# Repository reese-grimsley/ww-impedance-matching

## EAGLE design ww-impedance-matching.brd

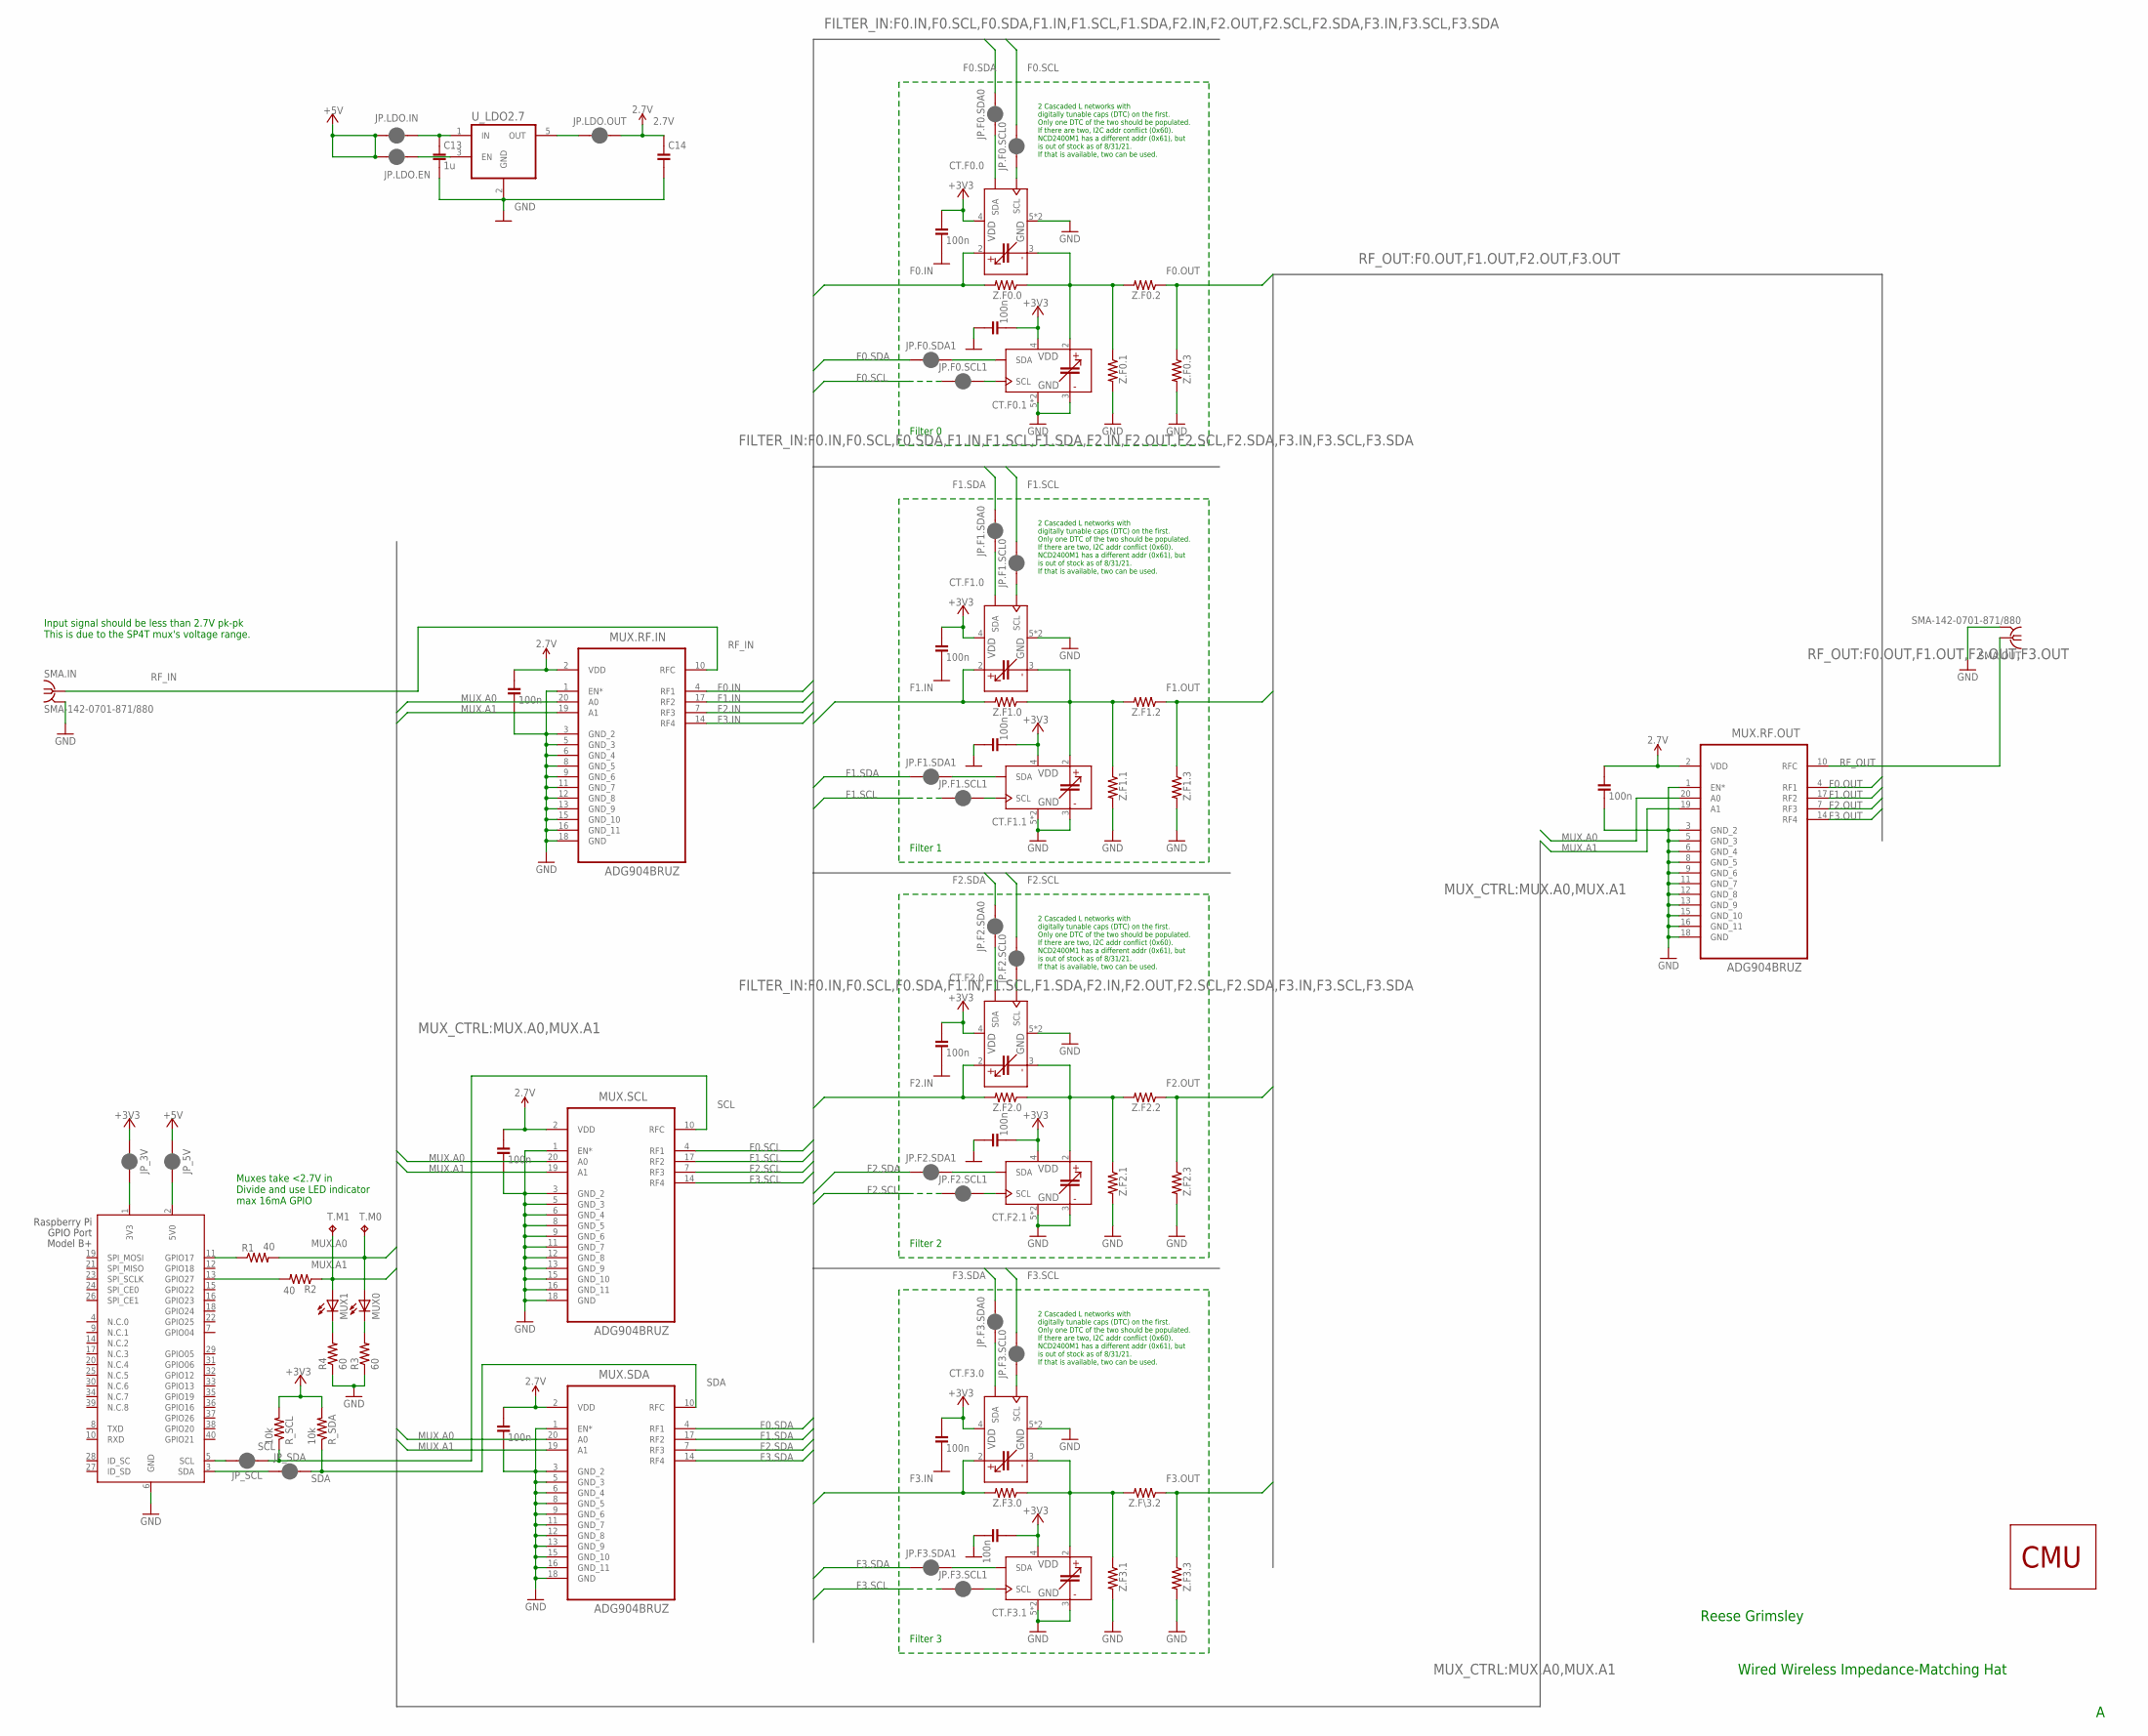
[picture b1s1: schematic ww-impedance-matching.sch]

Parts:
C1, C2, C3, C4, C5, C6, C7, C8, C9, C10, C11, C12: 100n; C0603; MPN CC0603MRX7R7BB104
C13: 1u; C0603; MPN CC0603MRX5R8BB105
C14: C-0805; C0805; MPN CC0805KPX5R6BB106
CT.F0.0, CT.F0.1, CT.F1.0, CT.F1.1, CT.F2.0, CT.F2.1, CT.F3.0, CT.F3.1: TUNABLE_CAP_NCD2400MTR; DFN-6_NCD2400M
JP.F0.SCL0, JP.F0.SCL1, JP.F0.SDA0, JP.F0.SDA1, JP.F1.SCL0, JP.F1.SCL1, JP.F1.SDA0, JP.F1.SDA1, JP.F2.SCL0, JP.F2.SCL1, JP.F2.SDA0, JP.F2.SDA1, JP.F3.SCL0, JP.F3.SCL1, JP.F3.SDA0, JP.F3.SDA1, JP.LDO.EN, JP.LDO.IN, JP.LDO.OUT: JUMPER-SMT_2_NC_PASTE_NO-SILK; SMT-JUMPER_2_NC_PASTE_NO-SILK
JP_3V, JP_5V: JUMPER-SMT_2_NC_PASTE_NO-SILK; SMT-JUMPER_2_NC_PASTE_NO-SILK
JP_SCL: JUMPER-SMT_2_NC_PASTE_NO-SILK; SMT-JUMPER_2_NC_PASTE_NO-SILK
JP_SDA: JUMPER-SMT_2_NC_PASTE_NO-SILK; SMT-JUMPER_2_NC_PASTE_NO-SILK
LOGO1: LOGO-CMU; CMU_LOGO
MUX0, MUX1: LEDCHIPLED_0603; CHIPLED_0603; MPN LSM0603412V
MUX.RF.IN, MUX.RF.OUT, MUX.SCL, MUX.SDA: ADG904BRUZ; SOP65P640X120-20N
R1, R2: 40; R0603; MPN ERJ-3EKF40R2V
R3, R4: 60; R0603; MPN ERJ-3EKF60R4V
R_SCL: 10k; R0603; MPN ERJ-PA3F1002V
R_SDA: 10k; R0603; MPN ERJ-PA3F1002V
SMA.IN, SMA.OUT: SMA-142-0701-871/880; SMA-142-0701-871; PART_NO 142-0701-871
T.M0, T.M1: TPTP14R; TP14R
U_LDO2.7: TPS76327DBVT; SOT95P280X145-5N; MPN TPS76327DBVT
X1: RASPI_BOARD_B+_E4P; RASPI_BOARD_B+_EDGES_4DRILL_PAD; MPN TSM-110-02-S-DV
Z.F0.0, Z.F0.1, Z.F0.2, Z.F0.3, Z.F1.0, Z.F1.1, Z.F1.2, Z.F1.3, Z.F2.0, Z.F2.1, Z.F2.2, Z.F2.3, Z.F3.0, Z.F3.1, Z.F3.3, Z.F\3.2: R-0603; R0603

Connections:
2.7V: C7.1, C9.1, C11.1, C12.1, C14.1, JP.LDO.OUT.1, MUX.RF.IN.2 (VDD), MUX.RF.OUT.2 (VDD), MUX.SCL.2 (VDD), MUX.SDA.2 (VDD)
3V3.JMP: JP_3V.1, X1.1 (3V3)
5V.JMP: JP_5V.1, X1.2 (5V0)
+3V3: C1.1, C2.2, C3.1, C4.1, C5.1, C6.2, C8.1, C10.2, CT.F0.0.4 (VDD), CT.F0.1.4 (VDD), CT.F1.0.4 (VDD), CT.F1.1.4 (VDD), CT.F2.0.4 (VDD), CT.F2.1.4 (VDD), CT.F3.0.4 (VDD), CT.F3.1.4 (VDD), JP_3V.2, R_SCL.2, R_SDA.2
+5V: JP.LDO.EN.2, JP.LDO.IN.2, JP_5V.2
F0.IN: CT.F0.0.2 (C+), MUX.RF.IN.4 (RF1), Z.F0.0.2
F0.OUT: MUX.RF.OUT.4 (RF1), Z.F0.2.1, Z.F0.3.1
F0.SCL: JP.F0.SCL0.1, JP.F0.SCL1.2, MUX.SCL.4 (RF1)
F0.SDA: JP.F0.SDA0.1, JP.F0.SDA1.2, MUX.SDA.4 (RF1)
F0SCL0: CT.F0.0.6 (SCL), JP.F0.SCL0.2
F0SCL1: CT.F0.1.6 (SCL), JP.F0.SCL1.1
F0SDA0: CT.F0.0.1 (SDA), JP.F0.SDA0.2
F0SDA1: CT.F0.1.1 (SDA), JP.F0.SDA1.1
F1.IN: CT.F1.0.2 (C+), MUX.RF.IN.17 (RF2), Z.F1.0.2
F1.OUT: MUX.RF.OUT.17 (RF2), Z.F1.2.1, Z.F1.3.1
F1.SCL: JP.F1.SCL0.1, JP.F1.SCL1.2, MUX.SCL.17 (RF2)
F1.SDA: JP.F1.SDA0.1, JP.F1.SDA1.2, MUX.SDA.17 (RF2)
F1SCL0: CT.F1.0.6 (SCL), JP.F1.SCL0.2
F1SCL1: CT.F1.1.6 (SCL), JP.F1.SCL1.1
F1SDA0: CT.F1.0.1 (SDA), JP.F1.SDA0.2
F1SDA1: CT.F1.1.1 (SDA), JP.F1.SDA1.1
F2.IN: CT.F2.0.2 (C+), MUX.RF.IN.7 (RF3), Z.F2.0.2
F2.OUT: MUX.RF.OUT.7 (RF3), Z.F2.2.1, Z.F2.3.1
F2.SCL: JP.F2.SCL0.1, JP.F2.SCL1.2, MUX.SCL.7 (RF3)
F2.SDA: JP.F2.SDA0.1, JP.F2.SDA1.2, MUX.SDA.7 (RF3)
F2SCL0: CT.F2.0.6 (SCL), JP.F2.SCL0.2
F2SCL1: CT.F2.1.6 (SCL), JP.F2.SCL1.1
F2SDA0: CT.F2.0.1 (SDA), JP.F2.SDA0.2
F2SDA1: CT.F2.1.1 (SDA), JP.F2.SDA1.1
F3.IN: CT.F3.0.2 (C+), MUX.RF.IN.14 (RF4), Z.F3.0.2
F3.OUT: MUX.RF.OUT.14 (RF4), Z.F3.3.1, Z.F\3.2.1
F3.SCL: JP.F3.SCL0.1, JP.F3.SCL1.2, MUX.SCL.14 (RF4)
F3.SDA: JP.F3.SDA0.1, JP.F3.SDA1.2, MUX.SDA.14 (RF4)
F3SCL0: CT.F3.0.6 (SCL), JP.F3.SCL0.2
F3SCL1: CT.F3.1.6 (SCL), JP.F3.SCL1.1
F3SDA0: CT.F3.0.1 (SDA), JP.F3.SDA0.2
F3SDA1: CT.F3.1.1 (SDA), JP.F3.SDA1.1
GND: C1.2, C2.1, C3.2, C4.2, C5.2, C6.1, C7.2, C8.2, C9.2, C10.1, C11.2, C12.2, C13.2, C14.2, CT.F0.0.5 (GND), CT.F0.0.7 (GND), CT.F0.1.3 (C-), CT.F0.1.5 (GND), CT.F0.1.7 (GND), CT.F1.0.5 (GND), CT.F1.0.7 (GND), CT.F1.1.3 (C-), CT.F1.1.5 (GND), CT.F1.1.7 (GND), CT.F2.0.5 (GND), CT.F2.0.7 (GND), CT.F2.1.3 (C-), CT.F2.1.5 (GND), CT.F2.1.7 (GND), CT.F3.0.5 (GND), CT.F3.0.7 (GND), CT.F3.1.3 (C-), CT.F3.1.5 (GND), CT.F3.1.7 (GND), MUX.RF.IN.1 (EN*), MUX.RF.IN.3 (GND_2), MUX.RF.IN.5 (GND_3), MUX.RF.IN.6 (GND_4), MUX.RF.IN.8 (GND_5), MUX.RF.IN.9 (GND_6), MUX.RF.IN.11 (GND_7), MUX.RF.IN.12 (GND_8), MUX.RF.IN.13 (GND_9), MUX.RF.IN.15 (GND_10), MUX.RF.IN.16 (GND_11), MUX.RF.IN.18 (GND), MUX.RF.OUT.1 (EN*), MUX.RF.OUT.3 (GND_2), MUX.RF.OUT.5 (GND_3), MUX.RF.OUT.6 (GND_4), MUX.RF.OUT.8 (GND_5), MUX.RF.OUT.9 (GND_6), MUX.RF.OUT.11 (GND_7), MUX.RF.OUT.12 (GND_8), MUX.RF.OUT.13 (GND_9), MUX.RF.OUT.15 (GND_10), MUX.RF.OUT.16 (GND_11), MUX.RF.OUT.18 (GND), MUX.SCL.1 (EN*), MUX.SCL.3 (GND_2), MUX.SCL.5 (GND_3), MUX.SCL.6 (GND_4), MUX.SCL.8 (GND_5), MUX.SCL.9 (GND_6), MUX.SCL.11 (GND_7), MUX.SCL.12 (GND_8), MUX.SCL.13 (GND_9), MUX.SCL.15 (GND_10), MUX.SCL.16 (GND_11), MUX.SCL.18 (GND), MUX.SDA.1 (EN*), MUX.SDA.3 (GND_2), MUX.SDA.5 (GND_3), MUX.SDA.6 (GND_4), MUX.SDA.8 (GND_5), MUX.SDA.9 (GND_6), MUX.SDA.11 (GND_7), MUX.SDA.12 (GND_8), MUX.SDA.13 (GND_9), MUX.SDA.15 (GND_10), MUX.SDA.16 (GND_11), MUX.SDA.18 (GND), R3.1, R4.1, SMA.IN.2@1 (2), SMA.IN.2@2 (2), SMA.IN.2@3 (2), SMA.IN.2@4 (2), SMA.OUT.2@1 (2), SMA.OUT.2@2 (2), SMA.OUT.2@3 (2), SMA.OUT.2@4 (2), U_LDO2.7.2 (GND), X1.6 (GND), Z.F0.1.2, Z.F0.3.2, Z.F1.1.2, Z.F1.3.2, Z.F2.1.2, Z.F2.3.2, Z.F3.1.2, Z.F3.3.2
LDO.IN: C13.1, JP.LDO.IN.1, U_LDO2.7.1 (IN)
LDO.OUT: JP.LDO.OUT.2, U_LDO2.7.5 (OUT)
MUX.A0: MUX0.A, MUX.RF.IN.20 (A0), MUX.RF.OUT.20 (A0), MUX.SCL.20 (A0), MUX.SDA.20 (A0), R1.2, T.M0.TP
MUX.A1: MUX1.A, MUX.RF.IN.19 (A1), MUX.RF.OUT.19 (A1), MUX.SCL.19 (A1), MUX.SDA.19 (A1), R2.1, T.M1.TP
unnamed: MUX1.C, R4.2
unnamed: JP.LDO.EN.1, U_LDO2.7.3 (EN)
unnamed: MUX0.C, R3.2
unnamed: R2.2, X1.13 (GPIO27)
unnamed: R1.1, X1.11 (GPIO17)
RF.F0.0: CT.F0.0.3 (C-), CT.F0.1.2 (C+), Z.F0.0.1, Z.F0.1.1, Z.F0.2.2
RF.F1.0: CT.F1.0.3 (C-), CT.F1.1.2 (C+), Z.F1.0.1, Z.F1.1.1, Z.F1.2.2
RF.F2.0: CT.F2.0.3 (C-), CT.F2.1.2 (C+), Z.F2.0.1, Z.F2.1.1, Z.F2.2.2
RF.F3.0: CT.F3.0.3 (C-), CT.F3.1.2 (C+), Z.F3.0.1, Z.F3.1.1, Z.F\3.2.2
RF_IN: MUX.RF.IN.10 (RFC), SMA.IN.1
RF_OUT: MUX.RF.OUT.10 (RFC), SMA.OUT.1
SCL: JP_SCL.2, MUX.SCL.10 (RFC), R_SCL.1
SCL.IN: JP_SCL.1, X1.5 (SCL)
SDA: JP_SDA.1, MUX.SDA.10 (RFC), R_SDA.1
SDA.IN: JP_SDA.2, X1.3 (SDA)

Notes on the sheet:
Wired Wireless Impedance-Matching Hat
Filter 0
2 Cascaded L networks with digitally tunable caps (DTC) on the first. Only one DTC of the two should be populated. If there are two, I2C addr conflict (0x60). NCD2400M1 has a different addr (0x61), but is out of stock as of 8/31/21. If that is available, two can be used.
Filter 1
Filter 2
Reese Grimsley
Filter 3
Muxes take <2.7V in Divide and use LED indicator max 16mA GPIO
Input signal should be less than 2.7V pk-pk This is due to the SP4T mux's voltage range.

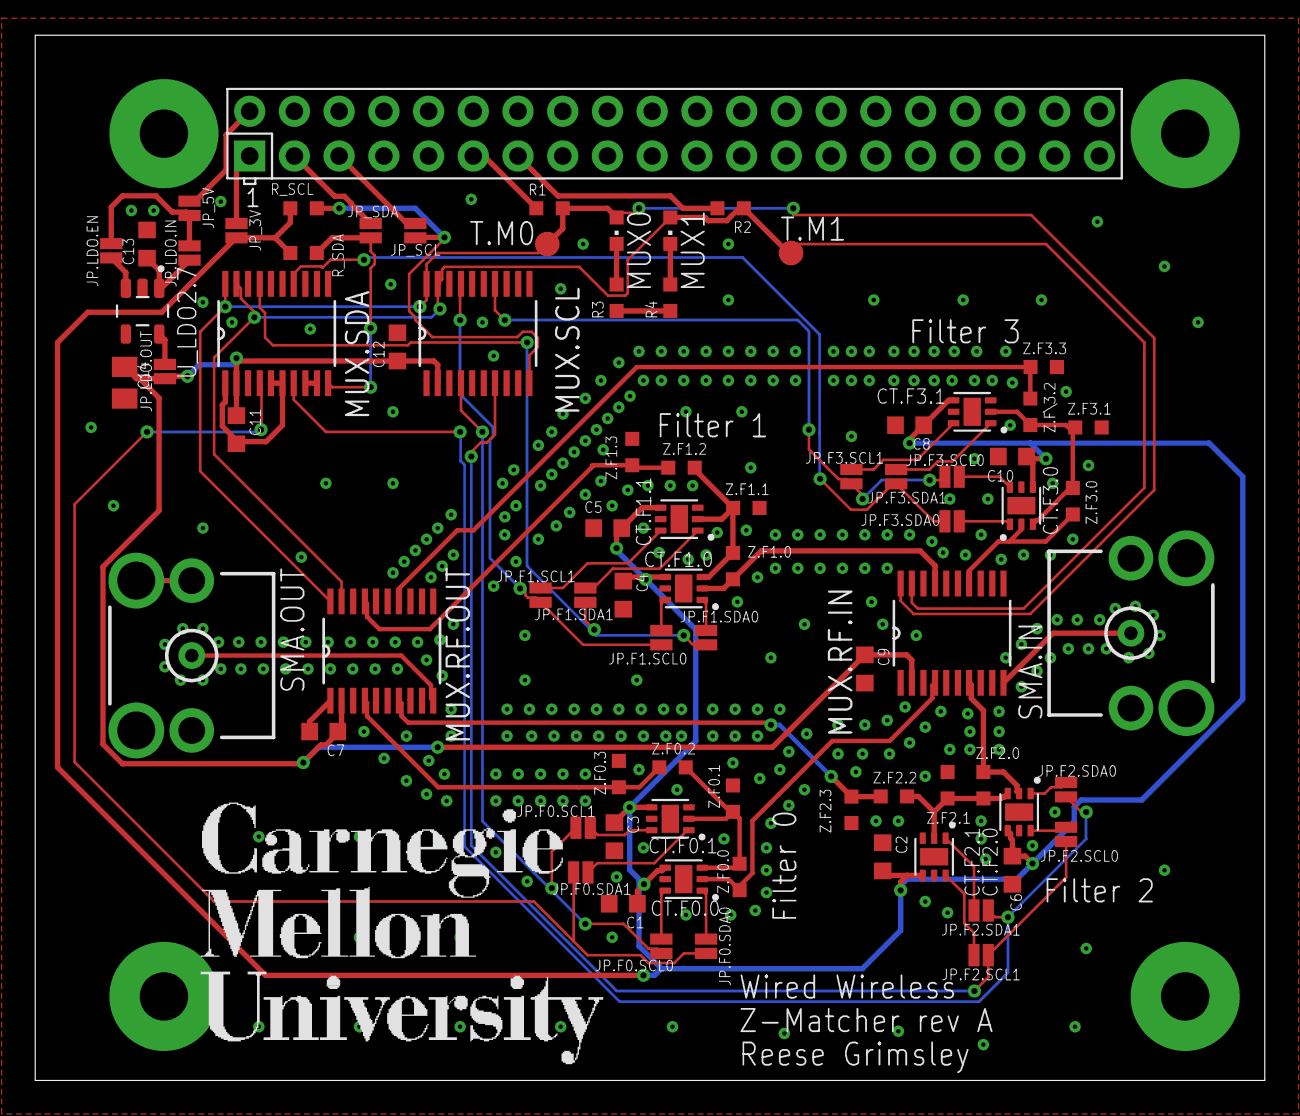
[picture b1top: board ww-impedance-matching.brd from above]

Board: 2 copper layers, 69.8 x 59.4 mm, 80 parts (0 on the bottom side), 57 nets.

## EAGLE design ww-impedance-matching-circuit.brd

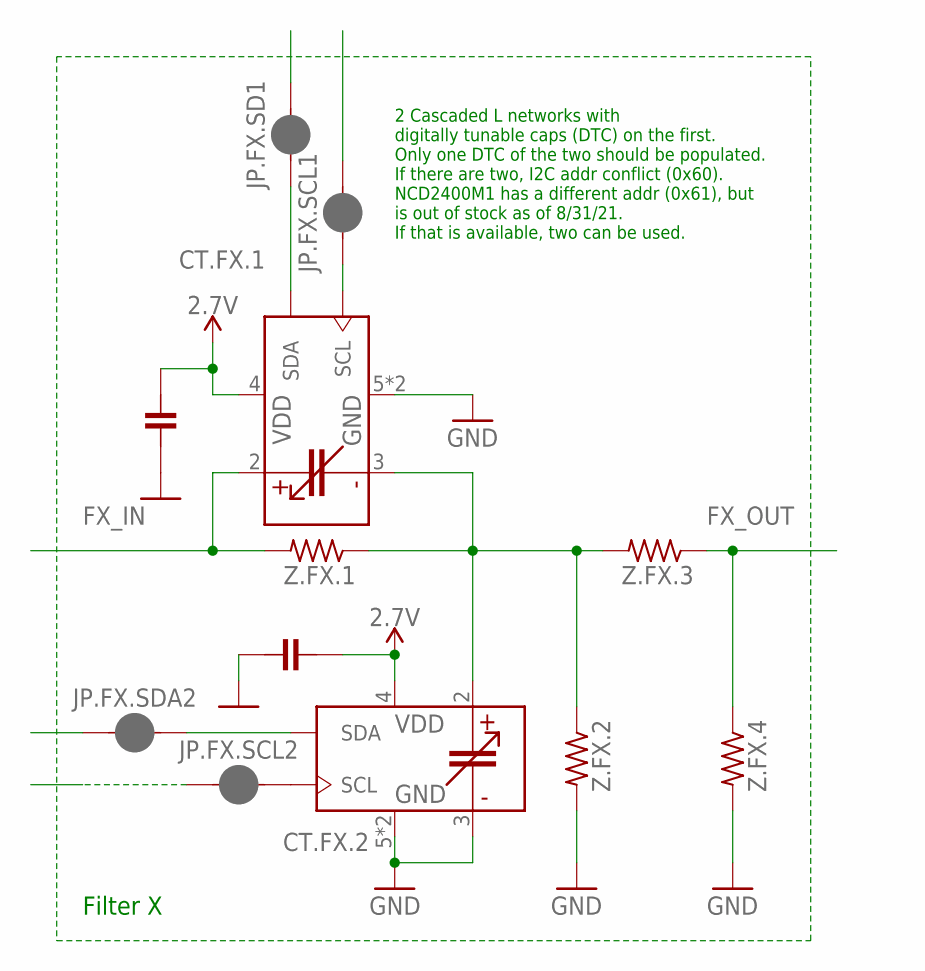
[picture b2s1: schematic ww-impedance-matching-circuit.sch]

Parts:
C1, C2: C-0603; C0603
CT.FX.1, CT.FX.2: TUNABLE_CAP_NCD2400MTR; DFN-6_NCD2400M
JP.FX.SCL1, JP.FX.SCL2, JP.FX.SD1, JP.FX.SDA2: JUMPER-SMT_2_NC_PASTE_NO-SILK; SMT-JUMPER_2_NC_PASTE_NO-SILK
Z.FX.1, Z.FX.2, Z.FX.3, Z.FX.4: R-0603; R0603

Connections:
2.7V: C1.1, C2.1, CT.FX.1.4 (VDD), CT.FX.2.4 (VDD)
FX_IN: CT.FX.1.2 (C+), Z.FX.1.2
FX_OUT: Z.FX.3.1, Z.FX.4.1
GND: C1.2, C2.2, CT.FX.1.5 (GND), CT.FX.1.7 (GND), CT.FX.2.3 (C-), CT.FX.2.5 (GND), CT.FX.2.7 (GND), Z.FX.2.2, Z.FX.4.2
unnamed: CT.FX.1.3 (C-), CT.FX.2.2 (C+), Z.FX.1.1, Z.FX.2.1, Z.FX.3.2
unnamed: CT.FX.1.1 (SDA), JP.FX.SD1.2
unnamed: CT.FX.2.1 (SDA), JP.FX.SDA2.1
unnamed: CT.FX.2.6 (SCL), JP.FX.SCL2.1
unnamed: CT.FX.1.6 (SCL), JP.FX.SCL1.2

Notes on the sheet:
Filter X
2 Cascaded L networks with digitally tunable caps (DTC) on the first. Only one DTC of the two should be populated. If there are two, I2C addr conflict (0x60). NCD2400M1 has a different addr (0x61), but is out of stock as of 8/31/21. If that is available, two can be used.

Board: 2 copper layers, 12 parts (0 on the bottom side), 9 nets, no tracks yet.

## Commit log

2021-09-01 first pass schematic
2021-09-01 gitignore
2021-09-01 schematic done, basic component placement
2021-09-01 filter placement
2021-09-01 ignore eagle files
2021-09-01 mostly routed
2021-09-01 routed and passed DRC
2021-09-01 ready to submit rev A for production
2021-09-01 add BOM
2021-09-02 revA production
2021-09-10 add basic rpi script
2021-09-10 add functions and main
2021-09-10 GPIO set mode
2021-09-11 i2c to caps

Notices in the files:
parts and their libraries:
SparkFun-PowerSymbols: Licensing: Creative Commons ShareAlike 4.0 International - https://creativecommons.org/licenses/by-sa/4.0
